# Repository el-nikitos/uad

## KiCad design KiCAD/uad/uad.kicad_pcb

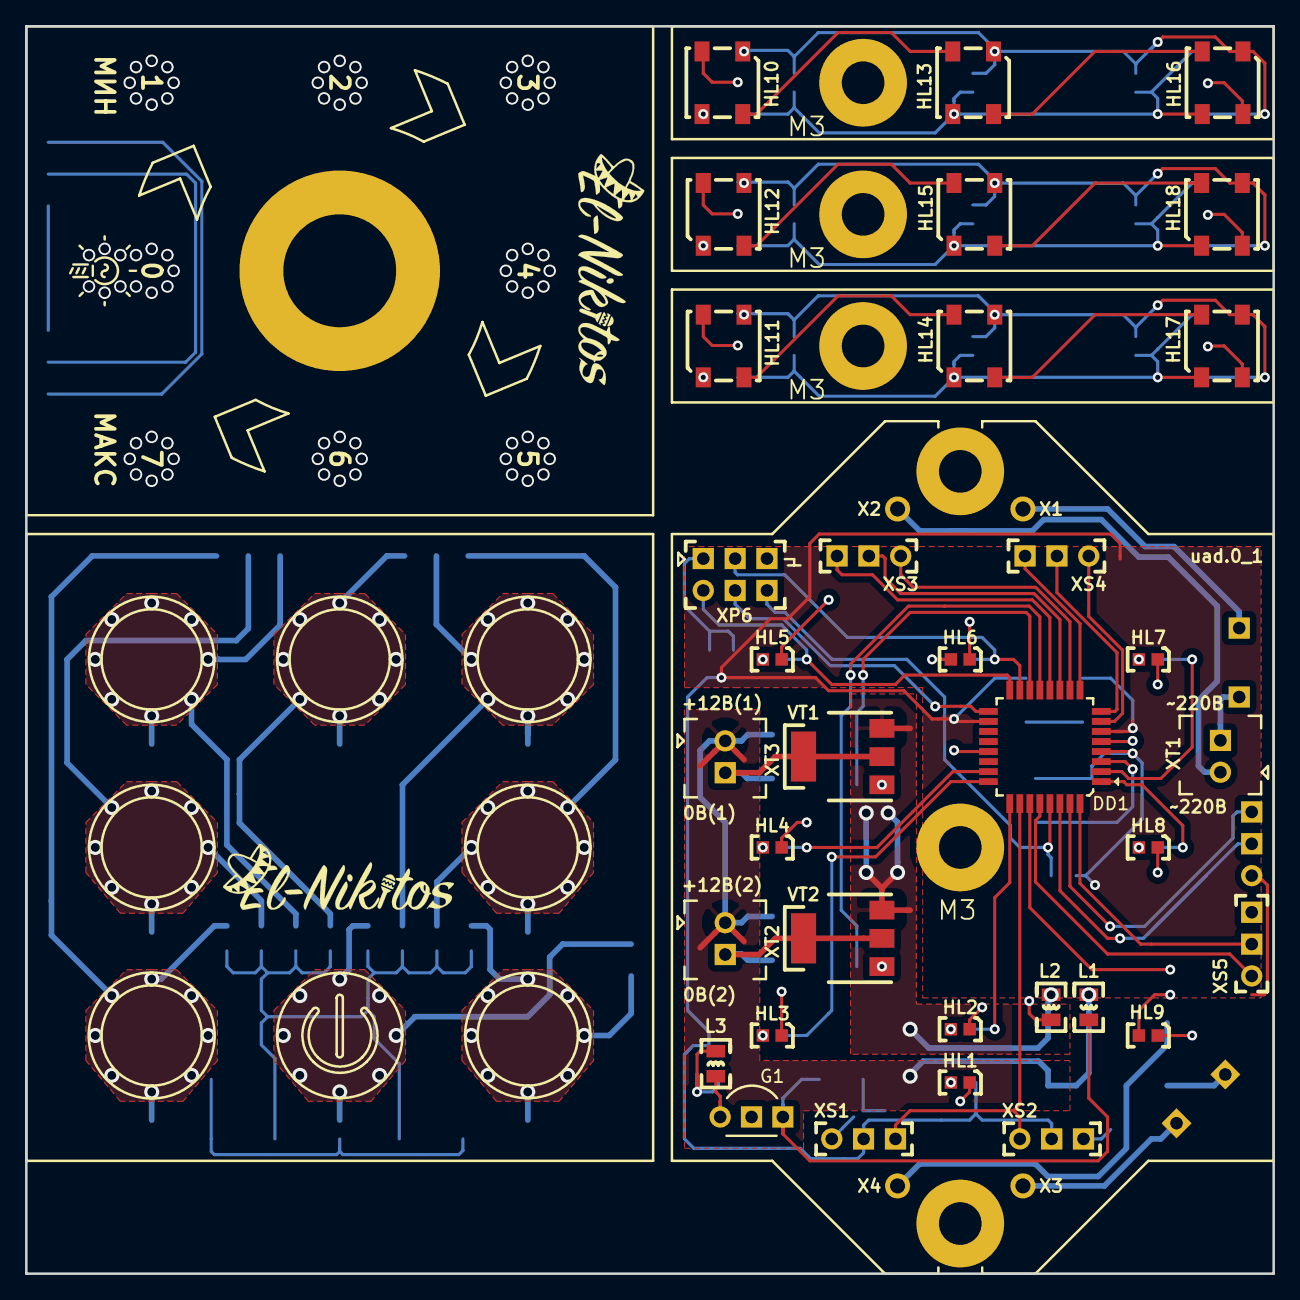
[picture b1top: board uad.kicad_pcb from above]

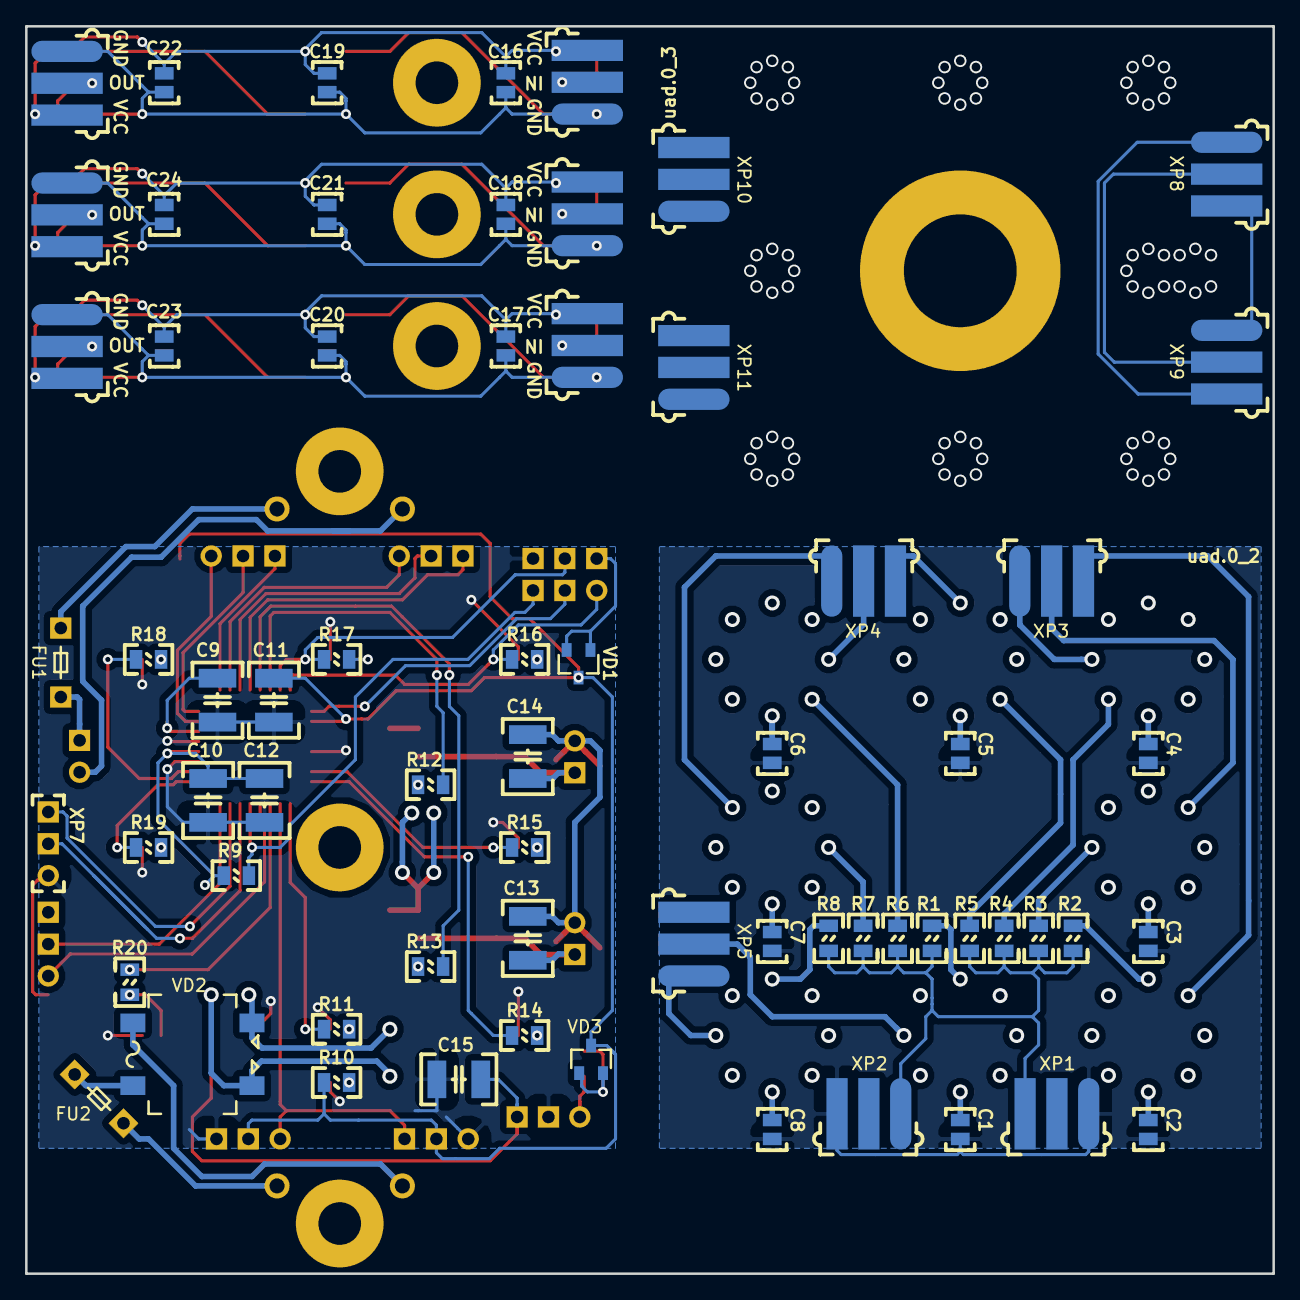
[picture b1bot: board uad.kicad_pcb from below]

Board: 2 copper layers, 99.5 x 99.5 mm, 110 parts (65 on the bottom side), 81 nets.

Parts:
C1, C2, C3, C4, C5, C6, C7, C8: 12пФ(0603); Конденсатор_SMD_0603
C9, C10, C11, C12, C13, C14, C15: 4.7мкФ(1210); Конденсатор_SMD_1210
C16, C17, C18, C19, C20, C21, C22, C23, C24: 100пФ(0603); Конденсатор_SMD_0603
DD1: ATmega8A-AU; микросхема_ATMEGA-8-161AU
FU1, FU2: Предохранитель; Предохранитель_MF-R_d10.4
G1: Стабилиатор_LM2931AZ-5.0G; Стабилизатор_корпус_TO-92
HL1, HL2, HL3, HL4, HL5, HL6, HL7, HL8, HL9: Светодиод; Светодиод_SMD_0603
HL10, HL11, HL12, HL13, HL14, HL15, HL16, HL17, HL18: Светодиод_NeoPixel; Светодиод_SMD_neopixel_ws2812b
L1, L2, L3: 33мкГн; Чип-индуктивность_SMD_0805
M3, M3#2, M3#3, M3#4, M3#5, M3#6: Отверстие_М3
M8: Отверстие_М8
R1, R2, R3, R4, R5, R6, R7, R8: 2 МОм(0805); Резистор_SMD_0805_0,125Вт
R9: 20 кОм(0805); Резистор_SMD_0805_0,125Вт
R10, R11, R14, R15, R16, R17, R18, R19, R20: 100 Ом(0805); Резистор_SMD_0805_0,125Вт
R12, R13: 300 Ом(0805); Резистор_SMD_0805_0,125Вт
VD1, VD3: Шоттки_BAR43CFILM; Диод_BAR43CFILM_SOT-23
VD2: Мост_DB155S; Диод_матрица_корпус_DB-1S
VT1, VT2: PBSS4540Z; Транзистор_NPN_SOT223
X1: L_220; ОтверстиеD1.2
X2: N_220; ОтверстиеD1.2
X3: L_12; ОтверстиеD1.2
X4: N_12; ОтверстиеD1.2
XP1, XP2, XP3, XP4, XP5, XP8, XP9, XP10, XP11, XP12, XP13, XP14, XP15, XP16, XP17: Вилка_PLS3; Вилка_PLS3_угловая_вертикальная
XP6: Вилка_PLD6_ПРОГ; Вилка_PLD6_вертикальная
XP7: Вилка_PLS3; Вилка_PLS3_вертикальная
XS1, XS2, XS3, XS4, XS5: Розетка_PBS3; Розетка_PBS3_вертикальная
XT1, XT2, XT3: Клеммник_х2; Клеммник_х2_шаг2.54

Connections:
/uab_logic/BUT_1_IN: DD1.32, XS5.2
/uab_logic/BUT_2_IN: DD1.12, XS3.3
/uab_logic/BUT_3_IN: DD1.11, XS3.2
/uab_logic/BUT_4_IN: DD1.10, XS3.1
/uab_logic/BUT_5_IN: DD1.9, XS4.3
/uab_logic/BUT_6_IN: DD1.8, XS4.2
/uab_logic/BUT_7_IN: DD1.7, XS4.1
/uab_logic/BUT_8_IN: DD1.28, XS5.1
/uab_logic/BUT_COM_OUT: DD1.26, XS1.3, XS2.1
/uab_logic/GND: C9.1, C10.1, C11.1, C12.1, C15.1, DD1.3, DD1.5, DD1.21, G1.2, HL1.2, HL2.2, HL3.2, HL4.2, HL5.2, HL6.2, HL7.2, HL8.2, HL9.2, L2.2, XP6.6, XP7.1, XS1.1, XS2.3
/uab_logic/L1: FU1.1, XT1.2
/uab_logic/L1_12: FU2.1, X3.1
/uab_logic/L2: FU1.2, X1.1
/uab_logic/L2_12: FU2.2, VD2.3
/uab_logic/LED_1: DD1.25, R11.1
/uab_logic/LED_2: DD1.24, R14.1
/uab_logic/LED_3: DD1.23, R15.1
/uab_logic/LED_4: DD1.16, R16.1, XP6.1
/uab_logic/LED_5: DD1.15, R17.1, XP6.4
/uab_logic/LED_6: DD1.2, R18.1
/uab_logic/LED_7: DD1.1, R19.1
/uab_logic/LED_8: DD1.27, R20.1
/uab_logic/N1: X2.1, XT1.1
/uab_logic/N1_12: VD2.4, X4.1
/uab_logic/PWM_OUT_1: DD1.14, R12.2
/uab_logic/PWM_OUT_2: DD1.13, R13.2
/uab_logic/PWR_12V: C13.2, C14.2, L1.1, VD2.1, XT2.1, XT3.1
/uab_logic/PWR_GND: L2.1, VD2.2, VT1.3, VT2.3
/uab_logic/RES: DD1.29, R9.2, XP6.5
/uab_logic/RX: DD1.30, XP7.2
/uab_logic/SCK: DD1.17, XP6.3
/uab_logic/TX: DD1.31, XP7.3
/uab_logic/VCC: C9.2, C10.2, C11.2, C12.2, DD1.4, DD1.6, DD1.18, R9.1, R10.1, VD1.2, VD3.2, XS1.2, XS2.2
/uab_logic/collector_1: C14.1, VT1.2, VT1.4, XT3.2
/uab_logic/collector_2: C13.1, VT2.2, VT2.4, XT2.2
/uad_analog_panel/BUT_COM_OUT: XP8.3, XP9.1
/uad_analog_panel/GND: XP8.1, XP9.3
/uad_analog_panel/VCC: XP8.2, XP9.2
/uad_sensor/BUT_1_CUP: C1.2, R1.2, XP5.2
/uad_sensor/BUT_2_CUP: C2.2, R2.2, XP3.3
/uad_sensor/BUT_3_CUP: C3.2, R3.2, XP3.2
/uad_sensor/BUT_4_CUP: C4.2, R4.2, XP3.1
/uad_sensor/BUT_5_CUP: C5.2, R5.2, XP4.3
/uad_sensor/BUT_6_CUP: C6.2, R6.2, XP4.2
/uad_sensor/BUT_7_CUP: C7.2, R7.2, XP4.1
/uad_sensor/BUT_8_CUP: C8.2, R8.2, XP5.1
/uad_sensor/BUT_COM_OUT: R1.1, R2.1, R3.1, R4.1, R5.1, R6.1, R7.1, R8.1, XP1.3, XP2.1
/uad_sensor/GND: C1.1, C2.1, C3.1, C4.1, C5.1, C6.1, C7.1, C8.1, XP1.1, XP2.3
unnamed: C15.2, G1.3, L1.2
unnamed: C16.1, C19.1, C22.1, HL10.3, HL13.3, HL16.3, XP12.3, XP15.3
unnamed: C16.2, C19.2, C22.2, HL10.1, HL13.1, HL16.1, XP12.1, XP15.1
unnamed: C17.1, C20.1, C23.1, HL11.3, HL14.3, HL17.3, XP13.3, XP16.3
unnamed: C17.2, C20.2, C23.2, HL11.1, HL14.1, HL17.1, XP13.1, XP16.1
unnamed: C18.1, C21.1, C24.1, HL12.3, HL15.3, HL18.3, XP14.3, XP17.3
unnamed: C18.2, C21.2, C24.2, HL12.1, HL15.1, HL18.1, XP14.1, XP17.1
unnamed: G1.1, L3.1
unnamed: HL1.1, R10.2
unnamed: HL2.1, R11.2
unnamed: HL3.1, R14.2
unnamed: HL4.1, R15.2
unnamed: HL5.1, R16.2
unnamed: HL6.1, R17.2
unnamed: HL7.1, R18.2
unnamed: HL8.1, R19.2
unnamed: HL9.1, R20.2
unnamed: HL10.2, HL13.4
unnamed: HL10.4, XP12.2
unnamed: HL11.2, HL14.4
unnamed: HL11.4, XP13.2
unnamed: HL12.2, HL15.4
unnamed: HL12.4, XP14.2
unnamed: HL13.2, HL16.4
unnamed: HL14.2, HL17.4
unnamed: HL15.2, HL18.4
unnamed: HL16.2, XP15.2
unnamed: HL17.2, XP16.2
unnamed: HL18.2, XP17.2
unnamed: L3.2, VD3.1
unnamed: R12.1, VT1.1
unnamed: R13.1, VT2.1
unnamed: VD1.1, XP6.2

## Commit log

2018-12-19 добавлена 3D-модель подрозетника
2018-12-21 начат проект платы сенсорной панели
2018-12-23 трассировка
    не расставлены резисторы/конденсатор емкостных кнопок
2018-12-24 переделана схема
    программирование совмещено с питанием
    выход на общую плату - дискретные выхода
2018-12-30 проект разбит на листы, лицевая панель расставлена, но не разведена
2018-12-30 разведена плата кнопок, плата контроллера - не расставлены светодиоды
2018-12-31 начато добавление клеммников на схему
2018-12-31 не поставлен эмиттерный повторитель на питание логики
2019-01-01 обе схемы закончены, разводка второй платы не закончена
2019-01-02 закончена разводка первого варианта (без отскока) и без фрезеровки
2019-01-03 в общий проект добавлена лицевая панель под потенциометр
2019-01-04 добавлены STEP и GERBER файлы
2019-01-04 добавлена примерка в Компас
2019-01-04 убрана фигурная фрезеровка. заменены GERBER файлы
2019-01-04 архив на отправку
2019-01-20 добавлен проект в AStudio
    -есть оцифровка потенциометра;
    -есть вывод шкалы индикации мощности;
    -нет вывода ШИМ;
    -нет переключения каналов ШИМ по таймеру;
2019-01-20 подготовка платы для заказа (уже заказана)
2019-01-21 добавлены 3D втулки и ручки
2019-01-23 начата реализация программного ШИМ
2019-01-24 первая версия с программным ШИМ готова, задержка переключения 70с
2019-02-02 нарисована переходная втулка и лицевая панель под поворотный регулятор
2019-02-02 начаты разворачиваться светодиоды
2019-02-03 корректировка декоративных частей (3D)
2019-02-10 добавлен габаритный чертеж
2019-02-13 на переходной втулке увеличена толщина узкого места
2019-06-01 переработка проекта под среду arduino
2019-06-01 перенесенная программа в среде arduino
    период 71 сек
    1 - только левый на полную
    2 - только правый на полную
    3...8 - пропорциональный режим от 5 до 12 В
    частота ШИМ ~2 кГц
